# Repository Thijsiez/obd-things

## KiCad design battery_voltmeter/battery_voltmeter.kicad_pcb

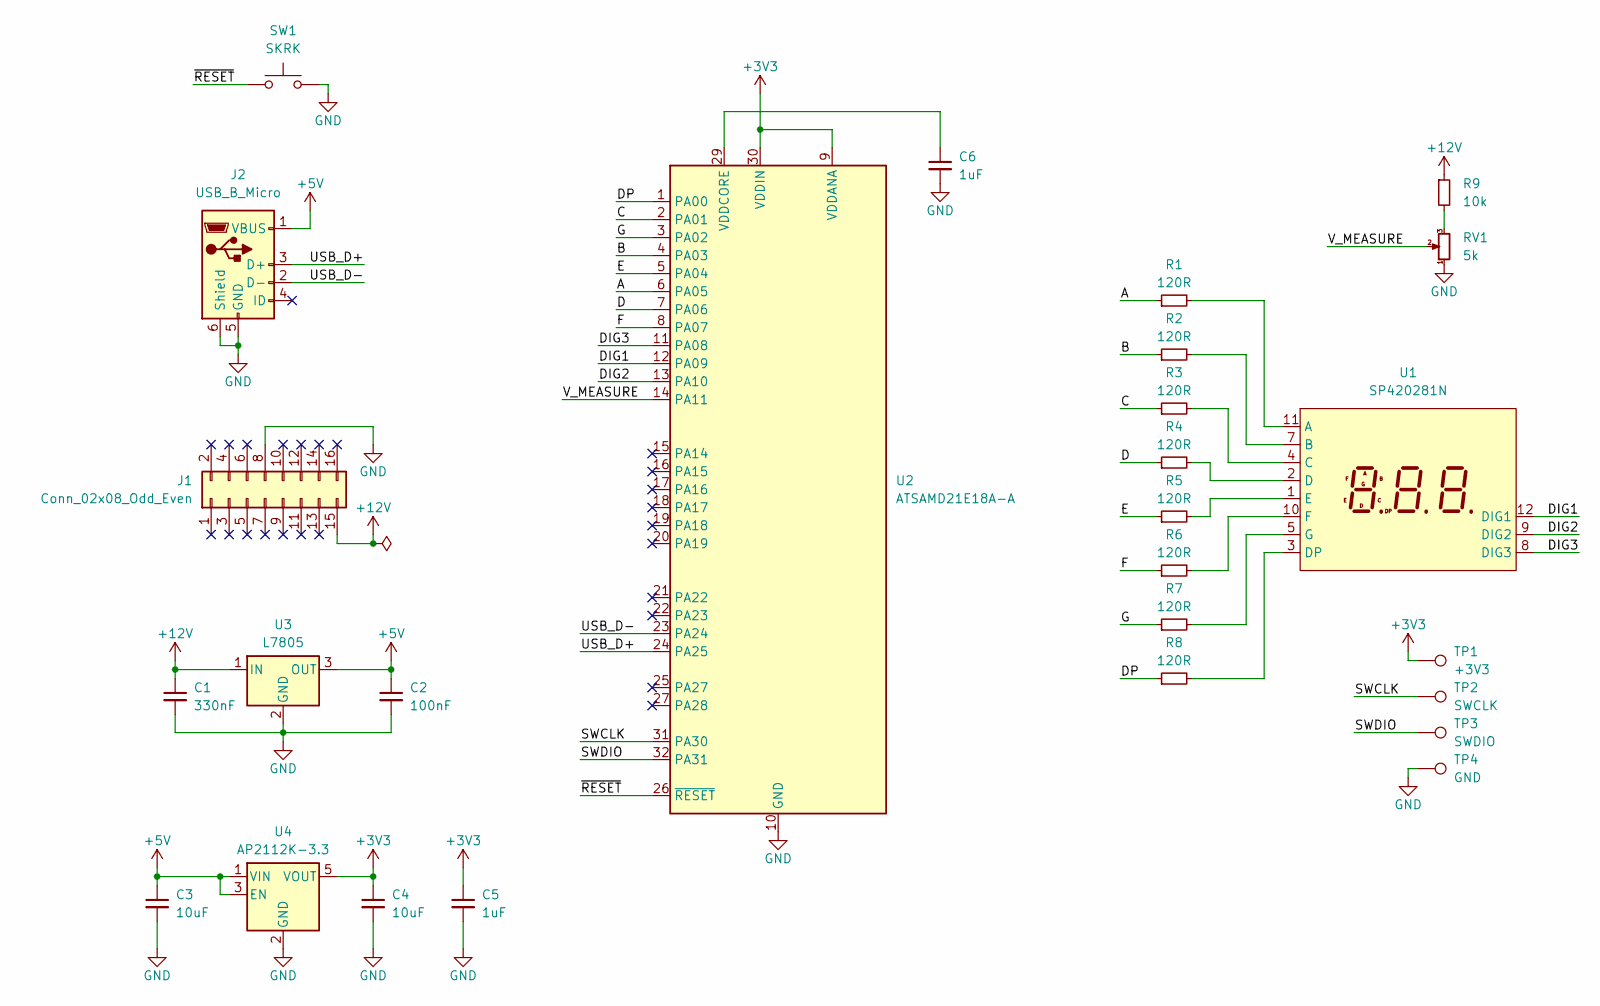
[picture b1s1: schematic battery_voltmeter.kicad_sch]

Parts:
C1: 330nF; C_0805_2012Metric_Pad1.18x1.45mm_HandSolder; LCSC C1740
C2: 100nF; C_0603_1608Metric_Pad1.08x0.95mm_HandSolder; LCSC C30926
C3, C4: 10uF; C_1206_3216Metric_Pad1.33x1.80mm_HandSolder; LCSC C90538
C5, C6: 1uF; C_0805_2012Metric_Pad1.18x1.45mm_HandSolder; LCSC C89190
J1: Conn_02x08_Odd_Even; PinSocket_2x08_P2.54mm_Vertical; LCSC C30734
J2: USB_B_Micro; USB_Micro-B_Molex-105133-0001; LCSC C586226
R1, R2, R3, R4, R5, R6, R7, R8: 120R; R_0603_1608Metric_Pad0.98x0.95mm_HandSolder; LCSC C22787
R9: 10k; R_0603_1608Metric_Pad0.98x0.95mm_HandSolder; LCSC C25804
RV1: 5k; Potentiometer_Bourns_3296W_Vertical; LCSC C118907
SW1: SKRK; SW_Push_SPST_NO_Alps_SKRK; LCSC C115357
TP1: +3V3; TestPoint_Pad_D1.0mm
TP2: SWCLK; TestPoint_Pad_D1.0mm
TP3: SWDIO; TestPoint_Pad_D1.0mm
TP4: GND; TestPoint_Pad_D1.0mm
U1: SP420281N; ARKLED_SP420281N; LCSC C122944
U2: ATSAMD21E18A-A; TQFP-32_7x7mm_P0.8mm; LCSC C1339245
U3: L7805; TO-252-2; LCSC C58069
U4: AP2112K-3.3; SOT-23-5; LCSC C51118

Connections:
+3V3: C4.1, C5.1, TP1.1, U2.9 (VDDANA), U2.30 (VDDIN), U4.5 (VOUT)
+5V: C2.1, C3.1, J2.1 (VBUS), U3.3 (OUT), U4.1 (VIN), U4.3 (EN)
+12V: C1.1, J1.15, R9.1, U3.1 (IN)
/A: R1.1, U2.6 (PA05)
/B: R2.1, U2.4 (PA03)
/C: R3.1, U2.2 (PA01)
/D: R4.1, U2.7 (PA06)
/DIG1: U1.12 (DIG1), U2.12 (PA09)
/DIG2: U1.9 (DIG2), U2.13 (PA10)
/DIG3: U1.8 (DIG3), U2.11 (PA08)
/DP: R8.1, U2.1 (PA00)
/E: R5.1, U2.5 (PA04)
/F: R6.1, U2.8 (PA07)
/G: R7.1, U2.3 (PA02)
/SWCLK: TP2.1, U2.31 (PA30)
/SWDIO: TP3.1, U2.32 (PA31)
/USB_D+: J2.3 (D+), U2.24 (PA25)
/USB_D-: J2.2 (D-), U2.23 (PA24)
/V_MEASURE: RV1.2, U2.14 (PA11)
/~RESET: SW1.1, U2.26 (~RESET)
GND: C1.2, C2.2, C3.2, C4.2, C5.2, C6.2, J1.8, J2.5 (GND), J2.6 (Shield), RV1.1, SW1.2, TP4.1, U2.10 (GND), U2.28 (GND), U3.2 (GND), U4.2 (GND)
unnamed: R9.2, RV1.3
unnamed: R1.2, U1.11 (A)
unnamed: R2.2, U1.7 (B)
unnamed: R3.2, U1.4 (C)
unnamed: R4.2, U1.2 (D)
unnamed: R8.2, U1.3 (DP)
unnamed: R5.2, U1.1 (E)
unnamed: R6.2, U1.10 (F)
unnamed: R7.2, U1.5 (G)
unnamed: C6.1, U2.29 (VDDCORE)

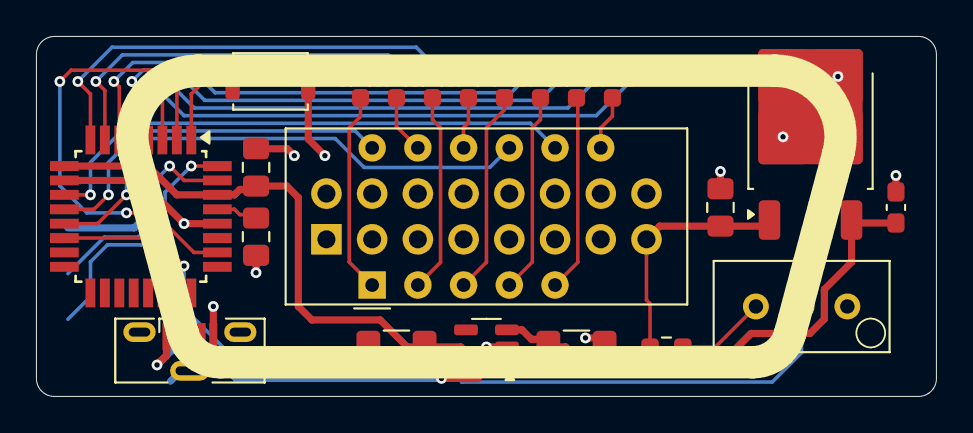
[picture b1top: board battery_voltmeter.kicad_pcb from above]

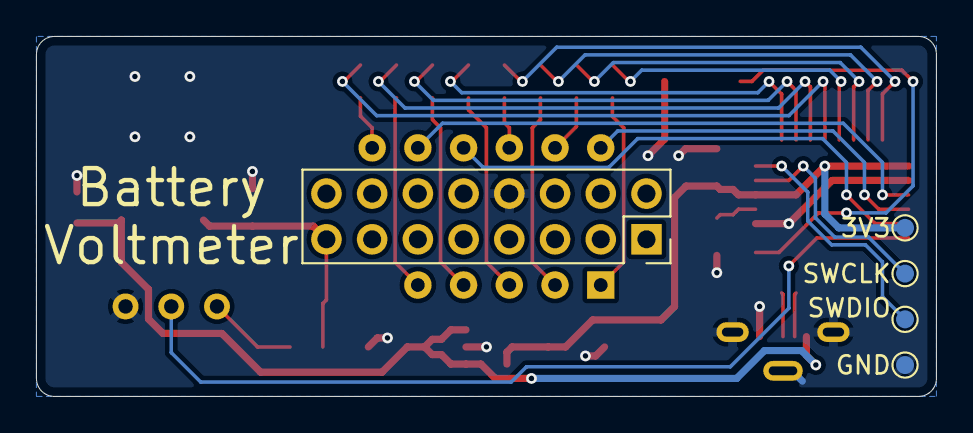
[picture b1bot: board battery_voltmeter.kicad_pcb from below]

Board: 2 copper layers, 50.0 x 20.0 mm, 27 parts (5 on the bottom side), 31 nets.

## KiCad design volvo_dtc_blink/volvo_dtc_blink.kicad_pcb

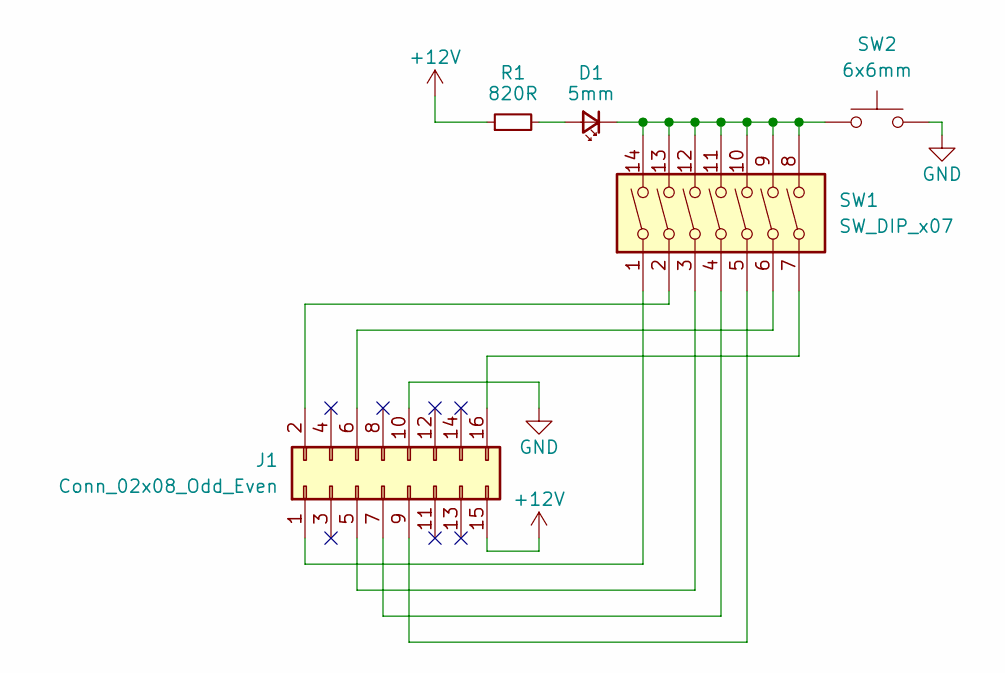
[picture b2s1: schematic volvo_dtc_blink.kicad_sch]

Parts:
D1: 5mm; LED_D5.0mm
J1: Conn_02x08_Odd_Even; PinSocket_2x08_P2.54mm_Vertical
R1: 820R; R_Axial_DIN0207_L6.3mm_D2.5mm_P2.54mm_Vertical
SW1: SW_DIP_x07; SW_DIP_SPSTx07_Slide_9.78x19.96mm_W7.62mm_P2.54mm
SW2: 6x6mm; SW_PUSH_6mm

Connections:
+12V: J1.15, R1.1
GND: J1.10, SW2.2
unnamed: D1.2 (A), R1.2
unnamed: D1.1 (K), SW1.8, SW1.9, SW1.10, SW1.11, SW1.12, SW1.13, SW1.14, SW2.1
unnamed: J1.1, SW1.1
unnamed: J1.2, SW1.2
unnamed: J1.5, SW1.3
unnamed: J1.6, SW1.6
unnamed: J1.7, SW1.4
unnamed: J1.9, SW1.5
unnamed: J1.16, SW1.7

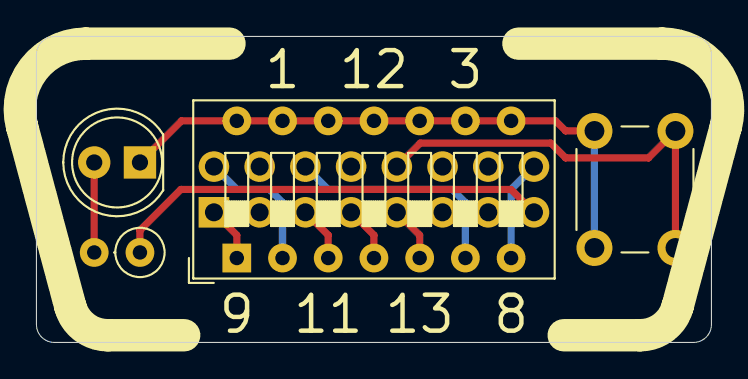
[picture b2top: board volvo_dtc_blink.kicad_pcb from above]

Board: 2 copper layers, 37.5 x 17.0 mm, 5 parts (1 on the bottom side), 11 nets.

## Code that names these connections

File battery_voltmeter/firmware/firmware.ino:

#define MEASURE PIN_PA11
#define MEASURE_INTERVAL_MILLIS 100

#define DIGITS 3
#define DIG1 PIN_PA09
#define DIG2 PIN_PA10
#define DIG3 PIN_PA08

#define SEGMENTS 7
#define SEG_A PIN_PA05
#define SEG_B PIN_PA03
#define SEG_C PIN_PA01
#define SEG_D PIN_PA06
#define SEG_E PIN_PA04
#define SEG_F PIN_PA07
#define SEG_G PIN_PA02
#define SEG_DOT PIN_PA00

const uint8_t digitPins[DIGITS] = {DIG1, DIG2, DIG3};
const uint8_t segmentPins[SEGMENTS] = {SEG_A, SEG_B, SEG_C, SEG_D, SEG_E, SEG_F, SEG_G};

const uint8_t segmentLookup[][SEGMENTS] = {
  //A     B     C     D     E     F     G
  {HIGH, HIGH, HIGH, HIGH, HIGH, HIGH, LOW }, //0
  {LOW , HIGH, HIGH, LOW , LOW , LOW , LOW }, //1
  {HIGH, HIGH, LOW , HIGH, HIGH, LOW , HIGH}, //2
  {HIGH, HIGH, HIGH, HIGH, LOW , LOW , HIGH}, //3
  {LOW , HIGH, HIGH, LOW , LOW , HIGH, HIGH}, //4
  {HIGH, LOW , HIGH, HIGH, LOW , HIGH, HIGH}, //5
  {HIGH, LOW , HIGH, HIGH, HIGH, HIGH, HIGH}, //6
  {HIGH, HIGH, HIGH, LOW , LOW , LOW , LOW }, //7
  {HIGH, HIGH, HIGH, HIGH, HIGH, HIGH, HIGH}, //8
  {HIGH, HIGH, HIGH, HIGH, LOW , HIGH, HIGH}, //9
};

unsigned long currentMillis;
unsigned long nextMeasurementMillis = 0;
uint8_t digitValue[DIGITS] = {0, 0, 0};

void setup() {
  analogReadResolution(12);
  pinMode(MEASURE, INPUT);
  for (uint8_t i = 0; i < DIGITS; i++) {
    pinMode(digitPins[i], OUTPUT);
    digitalWrite(digitPins[i], HIGH);
  }
  for (uint8_t i = 0; i < SEGMENTS; i++) {
    pinMode(segmentPins[i], OUTPUT);
    digitalWrite(segmentPins[i], LOW);
  }
  pinMode(SEG_DOT, OUTPUT);
  digitalWrite(SEG_DOT, LOW);
}

void loop() {
  currentMillis = millis();
  if (currentMillis > nextMeasurementMillis) {
    nextMeasurementMillis = currentMillis + MEASURE_INTERVAL_MILLIS;

    int mappedValue = map(analogRead(MEASURE), 0, 4095, 0, 200);
    digitValue[0] = mappedValue / 100;
    digitValue[1] = (mappedValue / 10) % 10;
    digitValue[2] = mappedValue % 10;
  }

  for (int i = 0; i < DIGITS; i++) {
    for (int j = 0; j < SEGMENTS; j++) {
      digitalWrite(segmentPins[j], segmentLookup[digitValue[i]][j]);
    }
    digitalWrite(SEG_DOT, i == 1);
    digitalWrite(digitPins[i], LOW);
    delay(3); //Leave the LEDs on for a little more brightness
    digitalWrite(digitPins[i], HIGH);
  }
}

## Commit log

2024-03-26 Add SAE J1962 breakout
2024-03-27 Add Volvo DTC blink module
2024-04-06 WIP battery voltmeter module
2024-04-07 WIP battery voltmeter module: part 2
2024-04-08 WIP battery voltmeter module: part 3
2024-04-10 Finish battery voltmeter module
2024-05-12 Fix component selection issue, add battery voltmeter firmware
2024-05-12 Fix serious voltage divider issue
2024-05-24 Set Battery Voltmeter ADC resolution to 12 bits
